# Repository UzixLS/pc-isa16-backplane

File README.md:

## ISA16-BACKPLANE
Compact ISA 16-bit backplane board

Specs:
- 171x155mm
- 7 ISA 16-bit (98 pin) slots
- ATX 20 pin power supply connector
- ATX power control circuit
- LEDs for +5V, +12V, -5V, -12V and standby power rails
- Power button
- Headers for power button and +5V power led

### Changelog
* Rev.A - first release
* Rev.A1 - ATX connector changed from 5.5mm to 4.4mm and rotated 180°

### See also
* ISA 8-bit backplane by Sergey Kiselev: [link](https://github.com/skiselev/isa8_backplane)
* ISA 16-bit backplane by Alexandru Groza: [link](https://alexandrugroza.ro/microelectronics/system-design/isa-backplane/index.html)

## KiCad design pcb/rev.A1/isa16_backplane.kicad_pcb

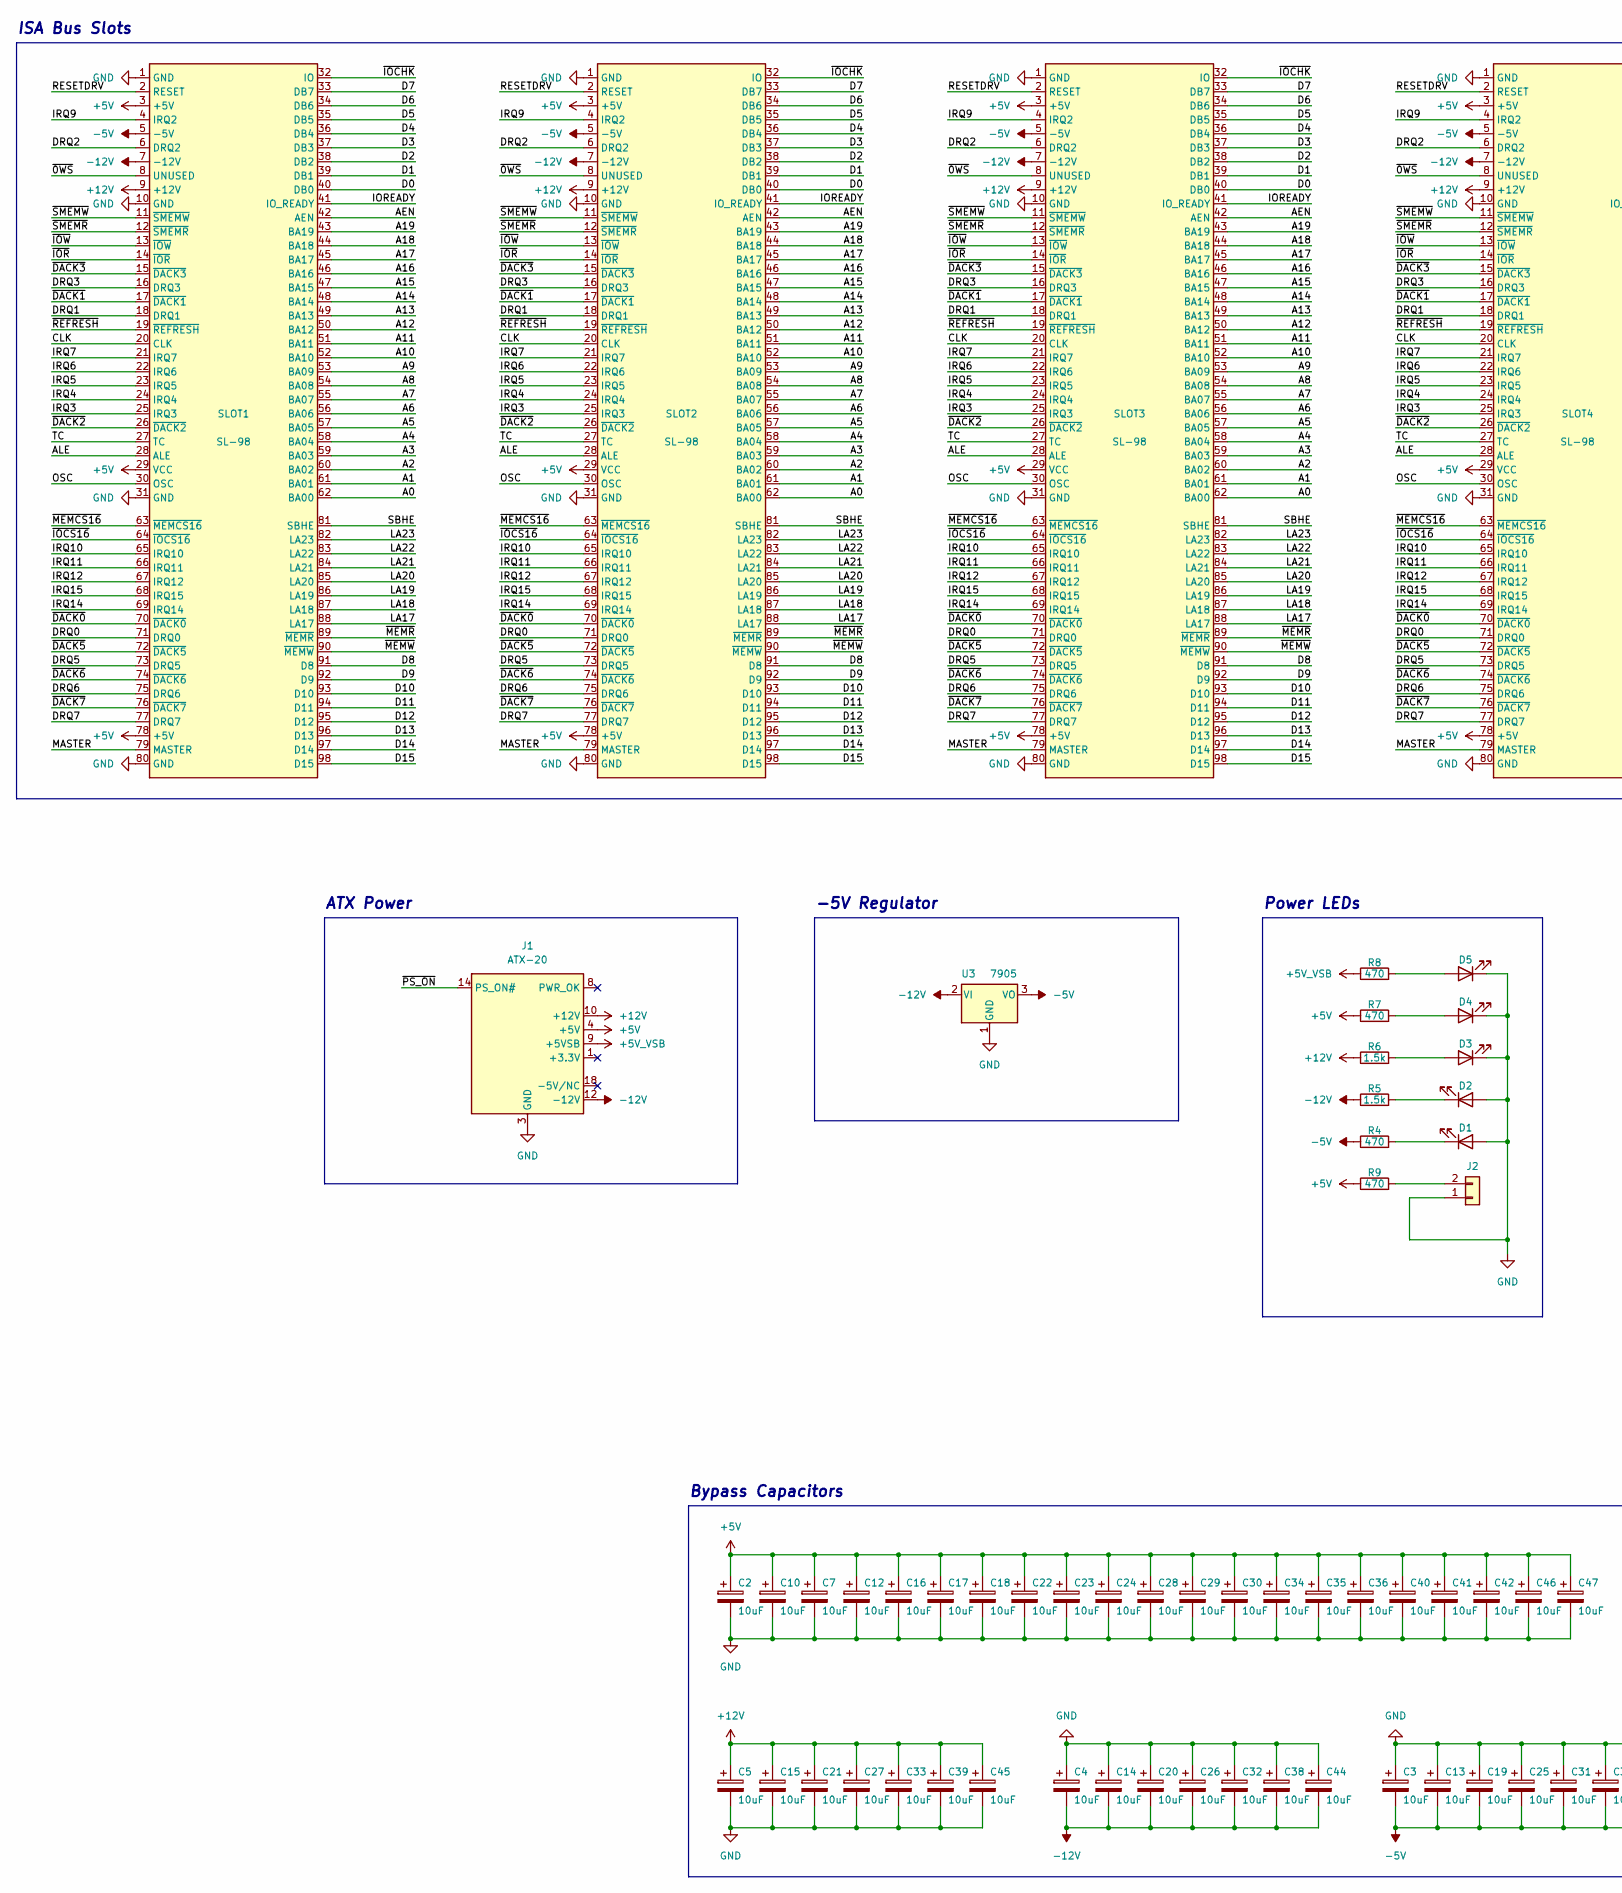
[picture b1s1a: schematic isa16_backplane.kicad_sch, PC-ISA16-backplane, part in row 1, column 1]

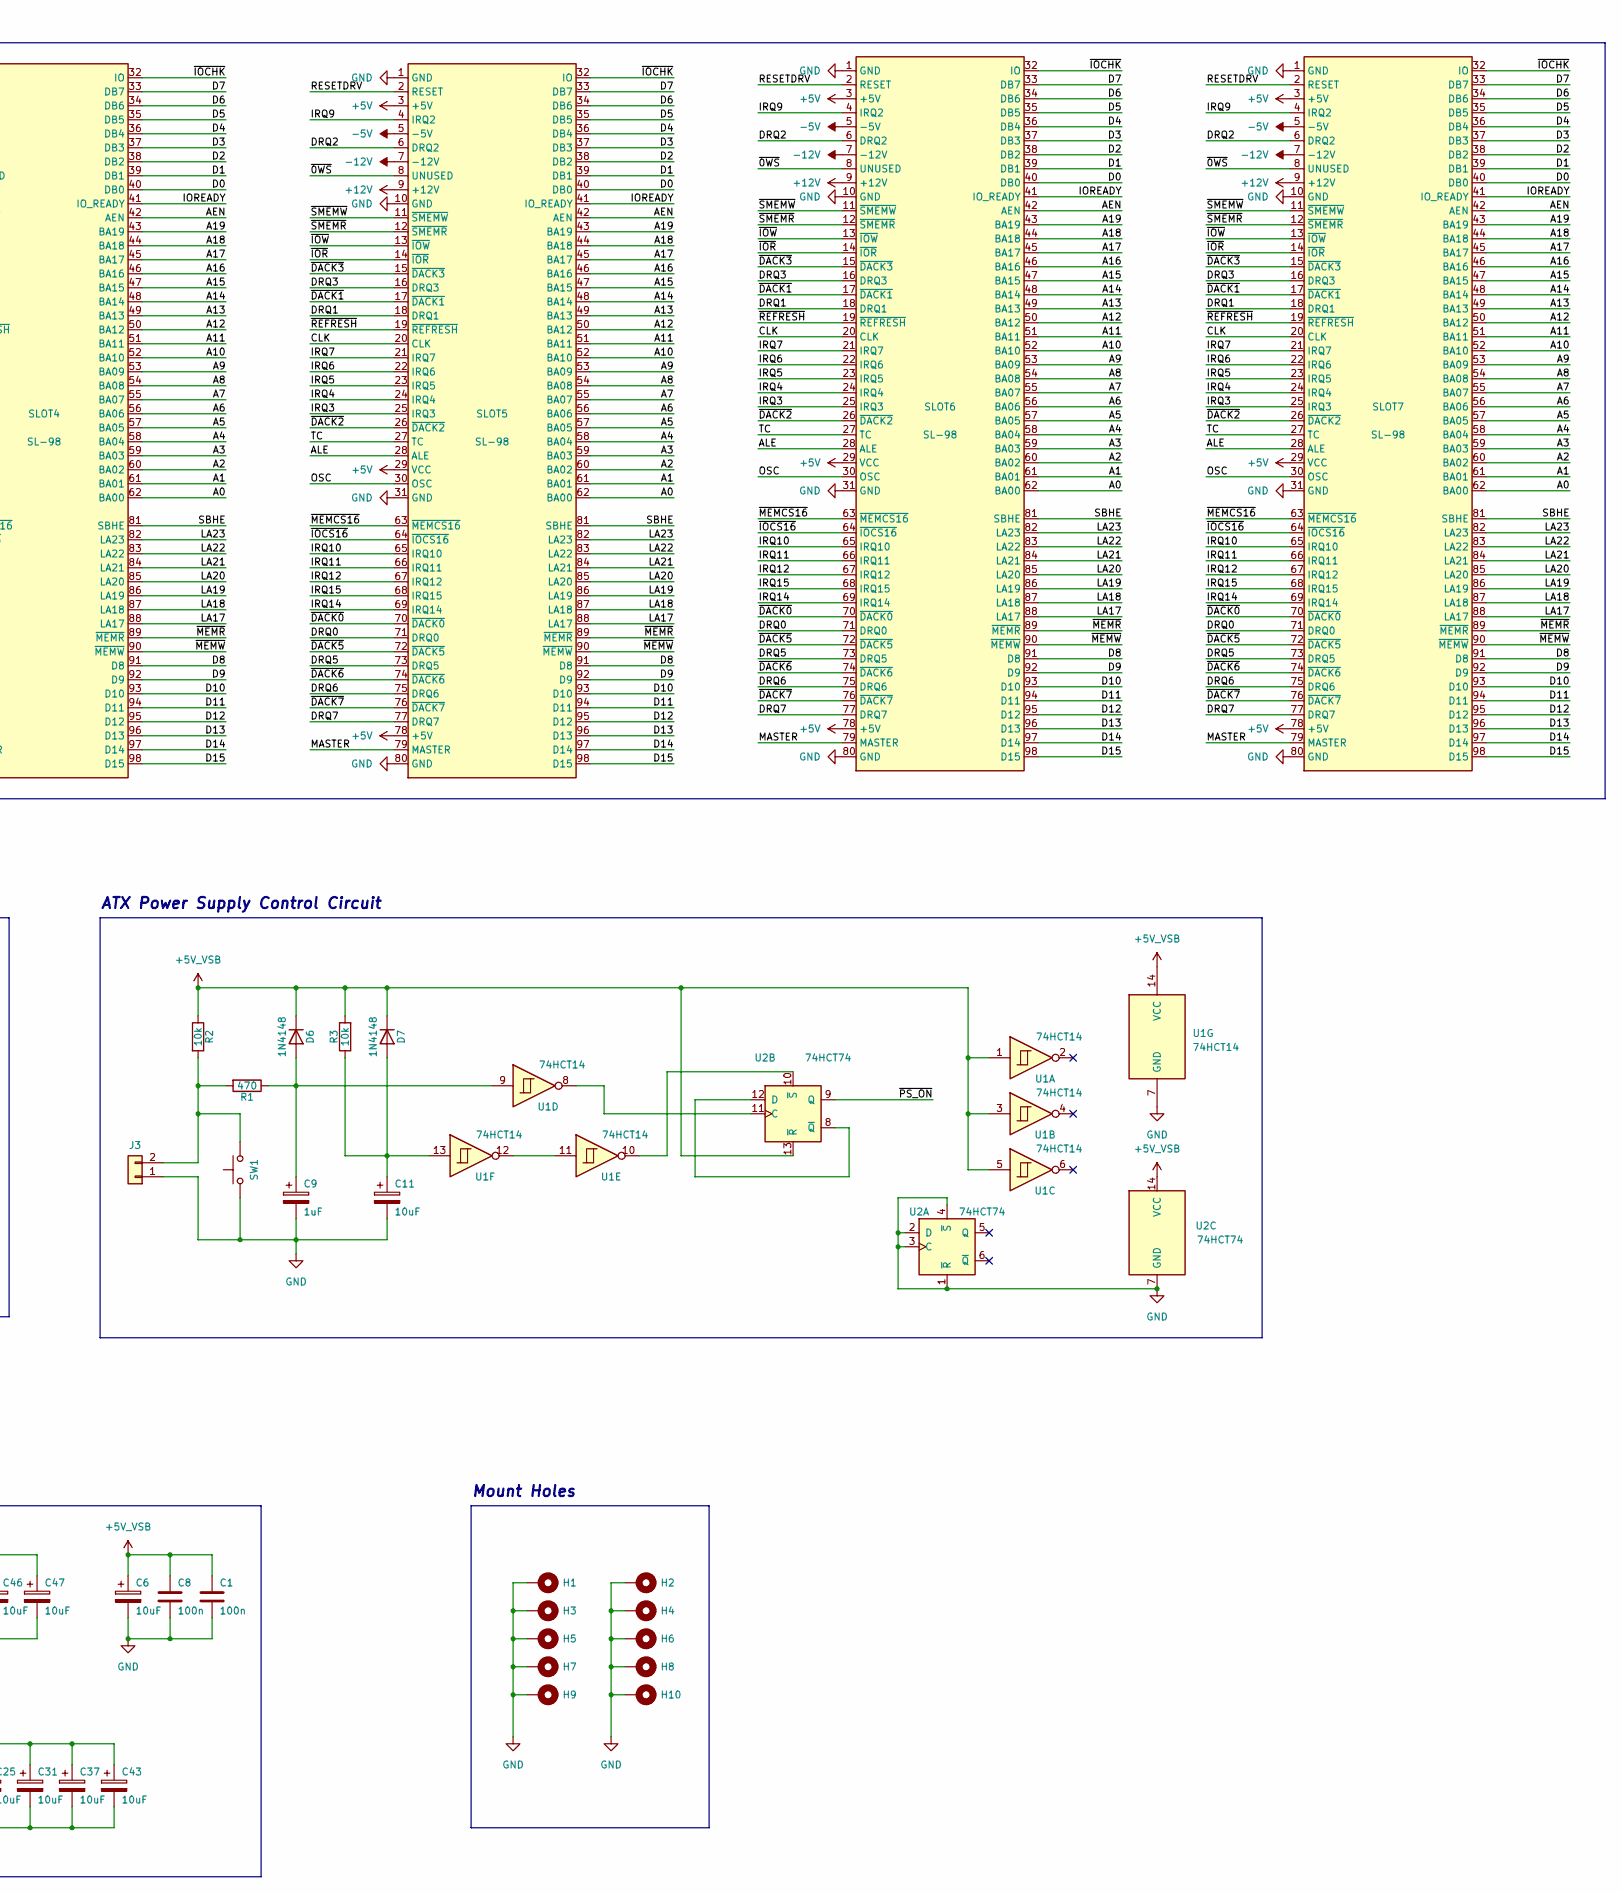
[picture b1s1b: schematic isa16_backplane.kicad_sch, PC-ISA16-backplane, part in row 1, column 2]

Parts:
C1, C8: 100n; C_Disc_D8.0mm_W2.5mm_P5.00mm
C2, C3, C4, C5, C6, C7, C10, C11, C12, C13, C14, C15, C16, C17, C18, C19, C20, C21, C22, C23, C24, C25, C26, C27, C28, C29, C30, C31, C32, C33, C34, C35, C36, C37, C38, C39, C40, C41, C42, C43, C44, C45, C46, C47: 10uF; CP_Radial_Tantal_D5.0mm_P5.00mm
C9: 1uF; CP_Radial_Tantal_D5.0mm_P5.00mm
D1, D2, D3, D4, D5: LED; LED_D5.0mm
D6, D7: 1N4148; D_DO-35_SOD27_P7.62mm_Horizontal
H1, H2, H3, H4, H5, H6, H7, H8, H9, H10: MountingHole_Pad; MountingHole_4mm_Pad_Via
J1: ATX-20; Conn_Power_ATX_20pin_4.4mm
J2, J3: Conn_01x02; PinHeader_1x02_P2.54mm_Vertical
R1, R4, R7, R8, R9: 470; R_Axial_DIN0207_L6.3mm_D2.5mm_P7.62mm_Horizontal
R2, R3: 10k; R_Axial_DIN0207_L6.3mm_D2.5mm_P7.62mm_Horizontal
R5, R6: 1.5k; R_Axial_DIN0207_L6.3mm_D2.5mm_P7.62mm_Horizontal
SLOT1, SLOT2, SLOT3, SLOT4, SLOT5, SLOT6, SLOT7: SL-98; ISA16_Slot
SW1: SW_Push; SW_PUSH_6mm
U1: 74HCT14; DIP-14_W7.62mm
U2: 74HCT74; DIP-14_W7.62mm
U3: 7905; TO-220-3_Horizontal_TabDownPin2

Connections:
+5V: C2.1, C7.1, C10.1, C12.1, C16.1, C17.1, C18.1, C22.1, C23.1, C24.1, C28.1, C29.1, C30.1, C34.1, C35.1, C36.1, C40.1, C41.1, C42.1, C46.1, C47.1, J1.4 (+5V), J1.6 (+5V), J1.19 (+5V), J1.20 (+5V), R7.1, R9.1, SLOT1.3 (+5V), SLOT1.29 (VCC), SLOT1.78 (+5V), SLOT2.3 (+5V), SLOT2.29 (VCC), SLOT2.78 (+5V), SLOT3.3 (+5V), SLOT3.29 (VCC), SLOT3.78 (+5V), SLOT4.3 (+5V), SLOT4.29 (VCC), SLOT4.78 (+5V), SLOT5.3 (+5V), SLOT5.29 (VCC), SLOT5.78 (+5V), SLOT6.3 (+5V), SLOT6.29 (VCC), SLOT6.78 (+5V), SLOT7.3 (+5V), SLOT7.29 (VCC), SLOT7.78 (+5V)
+5V_VSB: C1.1, C6.1, C8.1, D6.1 (K), D7.1 (K), J1.9 (+5VSB), R2.1, R3.2, R8.1, U1.1, U1.3, U1.5, U1.14 (VCC), U2.13 (~R), U2.14 (VCC)
+12V: C5.1, C15.1, C21.1, C27.1, C33.1, C39.1, C45.1, J1.10 (+12V), R6.1, SLOT1.9 (+12V), SLOT2.9 (+12V), SLOT3.9 (+12V), SLOT4.9 (+12V), SLOT5.9 (+12V), SLOT6.9 (+12V), SLOT7.9 (+12V)
-5V: C3.2, C13.2, C19.2, C25.2, C31.2, C37.2, C43.2, R4.1, SLOT1.5 (-5V), SLOT2.5 (-5V), SLOT3.5 (-5V), SLOT4.5 (-5V), SLOT5.5 (-5V), SLOT6.5 (-5V), SLOT7.5 (-5V), U3.3 (VO)
-12V: C4.2, C14.2, C20.2, C26.2, C32.2, C38.2, C44.2, J1.12 (-12V), R5.1, SLOT1.7 (-12V), SLOT2.7 (-12V), SLOT3.7 (-12V), SLOT4.7 (-12V), SLOT5.7 (-12V), SLOT6.7 (-12V), SLOT7.7 (-12V), U3.2 (VI)
/A0: SLOT1.62 (BA00), SLOT2.62 (BA00), SLOT3.62 (BA00), SLOT4.62 (BA00), SLOT5.62 (BA00), SLOT6.62 (BA00), SLOT7.62 (BA00)
/A1: SLOT1.61 (BA01), SLOT2.61 (BA01), SLOT3.61 (BA01), SLOT4.61 (BA01), SLOT5.61 (BA01), SLOT6.61 (BA01), SLOT7.61 (BA01)
/A2: SLOT1.60 (BA02), SLOT2.60 (BA02), SLOT3.60 (BA02), SLOT4.60 (BA02), SLOT5.60 (BA02), SLOT6.60 (BA02), SLOT7.60 (BA02)
/A3: SLOT1.59 (BA03), SLOT2.59 (BA03), SLOT3.59 (BA03), SLOT4.59 (BA03), SLOT5.59 (BA03), SLOT6.59 (BA03), SLOT7.59 (BA03)
/A4: SLOT1.58 (BA04), SLOT2.58 (BA04), SLOT3.58 (BA04), SLOT4.58 (BA04), SLOT5.58 (BA04), SLOT6.58 (BA04), SLOT7.58 (BA04)
/A5: SLOT1.57 (BA05), SLOT2.57 (BA05), SLOT3.57 (BA05), SLOT4.57 (BA05), SLOT5.57 (BA05), SLOT6.57 (BA05), SLOT7.57 (BA05)
/A6: SLOT1.56 (BA06), SLOT2.56 (BA06), SLOT3.56 (BA06), SLOT4.56 (BA06), SLOT5.56 (BA06), SLOT6.56 (BA06), SLOT7.56 (BA06)
/A7: SLOT1.55 (BA07), SLOT2.55 (BA07), SLOT3.55 (BA07), SLOT4.55 (BA07), SLOT5.55 (BA07), SLOT6.55 (BA07), SLOT7.55 (BA07)
/A8: SLOT1.54 (BA08), SLOT2.54 (BA08), SLOT3.54 (BA08), SLOT4.54 (BA08), SLOT5.54 (BA08), SLOT6.54 (BA08), SLOT7.54 (BA08)
/A9: SLOT1.53 (BA09), SLOT2.53 (BA09), SLOT3.53 (BA09), SLOT4.53 (BA09), SLOT5.53 (BA09), SLOT6.53 (BA09), SLOT7.53 (BA09)
/A10: SLOT1.52 (BA10), SLOT2.52 (BA10), SLOT3.52 (BA10), SLOT4.52 (BA10), SLOT5.52 (BA10), SLOT6.52 (BA10), SLOT7.52 (BA10)
/A11: SLOT1.51 (BA11), SLOT2.51 (BA11), SLOT3.51 (BA11), SLOT4.51 (BA11), SLOT5.51 (BA11), SLOT6.51 (BA11), SLOT7.51 (BA11)
/A12: SLOT1.50 (BA12), SLOT2.50 (BA12), SLOT3.50 (BA12), SLOT4.50 (BA12), SLOT5.50 (BA12), SLOT6.50 (BA12), SLOT7.50 (BA12)
/A13: SLOT1.49 (BA13), SLOT2.49 (BA13), SLOT3.49 (BA13), SLOT4.49 (BA13), SLOT5.49 (BA13), SLOT6.49 (BA13), SLOT7.49 (BA13)
/A14: SLOT1.48 (BA14), SLOT2.48 (BA14), SLOT3.48 (BA14), SLOT4.48 (BA14), SLOT5.48 (BA14), SLOT6.48 (BA14), SLOT7.48 (BA14)
/A15: SLOT1.47 (BA15), SLOT2.47 (BA15), SLOT3.47 (BA15), SLOT4.47 (BA15), SLOT5.47 (BA15), SLOT6.47 (BA15), SLOT7.47 (BA15)
/A16: SLOT1.46 (BA16), SLOT2.46 (BA16), SLOT3.46 (BA16), SLOT4.46 (BA16), SLOT5.46 (BA16), SLOT6.46 (BA16), SLOT7.46 (BA16)
/A17: SLOT1.45 (BA17), SLOT2.45 (BA17), SLOT3.45 (BA17), SLOT4.45 (BA17), SLOT5.45 (BA17), SLOT6.45 (BA17), SLOT7.45 (BA17)
/A18: SLOT1.44 (BA18), SLOT2.44 (BA18), SLOT3.44 (BA18), SLOT4.44 (BA18), SLOT5.44 (BA18), SLOT6.44 (BA18), SLOT7.44 (BA18)
/A19: SLOT1.43 (BA19), SLOT2.43 (BA19), SLOT3.43 (BA19), SLOT4.43 (BA19), SLOT5.43 (BA19), SLOT6.43 (BA19), SLOT7.43 (BA19)
/AEN: SLOT1.42 (AEN), SLOT2.42 (AEN), SLOT3.42 (AEN), SLOT4.42 (AEN), SLOT5.42 (AEN), SLOT6.42 (AEN), SLOT7.42 (AEN)
/ALE: SLOT1.28 (ALE), SLOT2.28 (ALE), SLOT3.28 (ALE), SLOT4.28 (ALE), SLOT5.28 (ALE), SLOT6.28 (ALE), SLOT7.28 (ALE)
/CLK: SLOT1.20 (CLK), SLOT2.20 (CLK), SLOT3.20 (CLK), SLOT4.20 (CLK), SLOT5.20 (CLK), SLOT6.20 (CLK), SLOT7.20 (CLK)
/D0: SLOT1.40 (DB0), SLOT2.40 (DB0), SLOT3.40 (DB0), SLOT4.40 (DB0), SLOT5.40 (DB0), SLOT6.40 (DB0), SLOT7.40 (DB0)
/D1: SLOT1.39 (DB1), SLOT2.39 (DB1), SLOT3.39 (DB1), SLOT4.39 (DB1), SLOT5.39 (DB1), SLOT6.39 (DB1), SLOT7.39 (DB1)
/D2: SLOT1.38 (DB2), SLOT2.38 (DB2), SLOT3.38 (DB2), SLOT4.38 (DB2), SLOT5.38 (DB2), SLOT6.38 (DB2), SLOT7.38 (DB2)
/D3: SLOT1.37 (DB3), SLOT2.37 (DB3), SLOT3.37 (DB3), SLOT4.37 (DB3), SLOT5.37 (DB3), SLOT6.37 (DB3), SLOT7.37 (DB3)
/D4: SLOT1.36 (DB4), SLOT2.36 (DB4), SLOT3.36 (DB4), SLOT4.36 (DB4), SLOT5.36 (DB4), SLOT6.36 (DB4), SLOT7.36 (DB4)
/D5: SLOT1.35 (DB5), SLOT2.35 (DB5), SLOT3.35 (DB5), SLOT4.35 (DB5), SLOT5.35 (DB5), SLOT6.35 (DB5), SLOT7.35 (DB5)
/D6: SLOT1.34 (DB6), SLOT2.34 (DB6), SLOT3.34 (DB6), SLOT4.34 (DB6), SLOT5.34 (DB6), SLOT6.34 (DB6), SLOT7.34 (DB6)
/D7: SLOT1.33 (DB7), SLOT2.33 (DB7), SLOT3.33 (DB7), SLOT4.33 (DB7), SLOT5.33 (DB7), SLOT6.33 (DB7), SLOT7.33 (DB7)
/D8: SLOT1.91 (D8), SLOT2.91 (D8), SLOT3.91 (D8), SLOT4.91 (D8), SLOT5.91 (D8), SLOT6.91 (D8), SLOT7.91 (D8)
/D9: SLOT1.92 (D9), SLOT2.92 (D9), SLOT3.92 (D9), SLOT4.92 (D9), SLOT5.92 (D9), SLOT6.92 (D9), SLOT7.92 (D9)
/D10: SLOT1.93 (D10), SLOT2.93 (D10), SLOT3.93 (D10), SLOT4.93 (D10), SLOT5.93 (D10), SLOT6.93 (D10), SLOT7.93 (D10)
/D11: SLOT1.94 (D11), SLOT2.94 (D11), SLOT3.94 (D11), SLOT4.94 (D11), SLOT5.94 (D11), SLOT6.94 (D11), SLOT7.94 (D11)
/D12: SLOT1.95 (D12), SLOT2.95 (D12), SLOT3.95 (D12), SLOT4.95 (D12), SLOT5.95 (D12), SLOT6.95 (D12), SLOT7.95 (D12)
/D13: SLOT1.96 (D13), SLOT2.96 (D13), SLOT3.96 (D13), SLOT4.96 (D13), SLOT5.96 (D13), SLOT6.96 (D13), SLOT7.96 (D13)
/D14: SLOT1.97 (D14), SLOT2.97 (D14), SLOT3.97 (D14), SLOT4.97 (D14), SLOT5.97 (D14), SLOT6.97 (D14), SLOT7.97 (D14)
/D15: SLOT1.98 (D15), SLOT2.98 (D15), SLOT3.98 (D15), SLOT4.98 (D15), SLOT5.98 (D15), SLOT6.98 (D15), SLOT7.98 (D15)
/DRQ0: SLOT1.71 (DRQ0), SLOT2.71 (DRQ0), SLOT3.71 (DRQ0), SLOT4.71 (DRQ0), SLOT5.71 (DRQ0), SLOT6.71 (DRQ0), SLOT7.71 (DRQ0)
/DRQ1: SLOT1.18 (DRQ1), SLOT2.18 (DRQ1), SLOT3.18 (DRQ1), SLOT4.18 (DRQ1), SLOT5.18 (DRQ1), SLOT6.18 (DRQ1), SLOT7.18 (DRQ1)
/DRQ2: SLOT1.6 (DRQ2), SLOT2.6 (DRQ2), SLOT3.6 (DRQ2), SLOT4.6 (DRQ2), SLOT5.6 (DRQ2), SLOT6.6 (DRQ2), SLOT7.6 (DRQ2)
/DRQ3: SLOT1.16 (DRQ3), SLOT2.16 (DRQ3), SLOT3.16 (DRQ3), SLOT4.16 (DRQ3), SLOT5.16 (DRQ3), SLOT6.16 (DRQ3), SLOT7.16 (DRQ3)
/DRQ5: SLOT1.73 (DRQ5), SLOT2.73 (DRQ5), SLOT3.73 (DRQ5), SLOT4.73 (DRQ5), SLOT5.73 (DRQ5), SLOT6.73 (DRQ5), SLOT7.73 (DRQ5)
/DRQ6: SLOT1.75 (DRQ6), SLOT2.75 (DRQ6), SLOT3.75 (DRQ6), SLOT4.75 (DRQ6), SLOT5.75 (DRQ6), SLOT6.75 (DRQ6), SLOT7.75 (DRQ6)
/DRQ7: SLOT1.77 (DRQ7), SLOT2.77 (DRQ7), SLOT3.77 (DRQ7), SLOT4.77 (DRQ7), SLOT5.77 (DRQ7), SLOT6.77 (DRQ7), SLOT7.77 (DRQ7)
/IOREADY: SLOT1.41 (IO_READY), SLOT2.41 (IO_READY), SLOT3.41 (IO_READY), SLOT4.41 (IO_READY), SLOT5.41 (IO_READY), SLOT6.41 (IO_READY), SLOT7.41 (IO_READY)
/IRQ3: SLOT1.25 (IRQ3), SLOT2.25 (IRQ3), SLOT3.25 (IRQ3), SLOT4.25 (IRQ3), SLOT5.25 (IRQ3), SLOT6.25 (IRQ3), SLOT7.25 (IRQ3)
/IRQ4: SLOT1.24 (IRQ4), SLOT2.24 (IRQ4), SLOT3.24 (IRQ4), SLOT4.24 (IRQ4), SLOT5.24 (IRQ4), SLOT6.24 (IRQ4), SLOT7.24 (IRQ4)
/IRQ5: SLOT1.23 (IRQ5), SLOT2.23 (IRQ5), SLOT3.23 (IRQ5), SLOT4.23 (IRQ5), SLOT5.23 (IRQ5), SLOT6.23 (IRQ5), SLOT7.23 (IRQ5)
/IRQ6: SLOT1.22 (IRQ6), SLOT2.22 (IRQ6), SLOT3.22 (IRQ6), SLOT4.22 (IRQ6), SLOT5.22 (IRQ6), SLOT6.22 (IRQ6), SLOT7.22 (IRQ6)
/IRQ7: SLOT1.21 (IRQ7), SLOT2.21 (IRQ7), SLOT3.21 (IRQ7), SLOT4.21 (IRQ7), SLOT5.21 (IRQ7), SLOT6.21 (IRQ7), SLOT7.21 (IRQ7)
/IRQ9: SLOT1.4 (IRQ2), SLOT2.4 (IRQ2), SLOT3.4 (IRQ2), SLOT4.4 (IRQ2), SLOT5.4 (IRQ2), SLOT6.4 (IRQ2), SLOT7.4 (IRQ2)
/IRQ10: SLOT1.65 (IRQ10), SLOT2.65 (IRQ10), SLOT3.65 (IRQ10), SLOT4.65 (IRQ10), SLOT5.65 (IRQ10), SLOT6.65 (IRQ10), SLOT7.65 (IRQ10)
/IRQ11: SLOT1.66 (IRQ11), SLOT2.66 (IRQ11), SLOT3.66 (IRQ11), SLOT4.66 (IRQ11), SLOT5.66 (IRQ11), SLOT6.66 (IRQ11), SLOT7.66 (IRQ11)
/IRQ12: SLOT1.67 (IRQ12), SLOT2.67 (IRQ12), SLOT3.67 (IRQ12), SLOT4.67 (IRQ12), SLOT5.67 (IRQ12), SLOT6.67 (IRQ12), SLOT7.67 (IRQ12)
/IRQ14: SLOT1.69 (IRQ14), SLOT2.69 (IRQ14), SLOT3.69 (IRQ14), SLOT4.69 (IRQ14), SLOT5.69 (IRQ14), SLOT6.69 (IRQ14), SLOT7.69 (IRQ14)
/IRQ15: SLOT1.68 (IRQ15), SLOT2.68 (IRQ15), SLOT3.68 (IRQ15), SLOT4.68 (IRQ15), SLOT5.68 (IRQ15), SLOT6.68 (IRQ15), SLOT7.68 (IRQ15)
/LA17: SLOT1.88 (LA17), SLOT2.88 (LA17), SLOT3.88 (LA17), SLOT4.88 (LA17), SLOT5.88 (LA17), SLOT6.88 (LA17), SLOT7.88 (LA17)
/LA18: SLOT1.87 (LA18), SLOT2.87 (LA18), SLOT3.87 (LA18), SLOT4.87 (LA18), SLOT5.87 (LA18), SLOT6.87 (LA18), SLOT7.87 (LA18)
/LA19: SLOT1.86 (LA19), SLOT2.86 (LA19), SLOT3.86 (LA19), SLOT4.86 (LA19), SLOT5.86 (LA19), SLOT6.86 (LA19), SLOT7.86 (LA19)
/LA20: SLOT1.85 (LA20), SLOT2.85 (LA20), SLOT3.85 (LA20), SLOT4.85 (LA20), SLOT5.85 (LA20), SLOT6.85 (LA20), SLOT7.85 (LA20)
/LA21: SLOT1.84 (LA21), SLOT2.84 (LA21), SLOT3.84 (LA21), SLOT4.84 (LA21), SLOT5.84 (LA21), SLOT6.84 (LA21), SLOT7.84 (LA21)
/LA22: SLOT1.83 (LA22), SLOT2.83 (LA22), SLOT3.83 (LA22), SLOT4.83 (LA22), SLOT5.83 (LA22), SLOT6.83 (LA22), SLOT7.83 (LA22)
/LA23: SLOT1.82 (LA23), SLOT2.82 (LA23), SLOT3.82 (LA23), SLOT4.82 (LA23), SLOT5.82 (LA23), SLOT6.82 (LA23), SLOT7.82 (LA23)
/MASTER: SLOT1.79 (MASTER), SLOT2.79 (MASTER), SLOT3.79 (MASTER), SLOT4.79 (MASTER), SLOT5.79 (MASTER), SLOT6.79 (MASTER), SLOT7.79 (MASTER)
/OSC: SLOT1.30 (OSC), SLOT2.30 (OSC), SLOT3.30 (OSC), SLOT4.30 (OSC), SLOT5.30 (OSC), SLOT6.30 (OSC), SLOT7.30 (OSC)
/RESETDRV: SLOT1.2 (RESET), SLOT2.2 (RESET), SLOT3.2 (RESET), SLOT4.2 (RESET), SLOT5.2 (RESET), SLOT6.2 (RESET), SLOT7.2 (RESET)
/SBHE: SLOT1.81 (SBHE), SLOT2.81 (SBHE), SLOT3.81 (SBHE), SLOT4.81 (SBHE), SLOT5.81 (SBHE), SLOT6.81 (SBHE), SLOT7.81 (SBHE)
/TC: SLOT1.27 (TC), SLOT2.27 (TC), SLOT3.27 (TC), SLOT4.27 (TC), SLOT5.27 (TC), SLOT6.27 (TC), SLOT7.27 (TC)
/~0WS: SLOT1.8 (UNUSED), SLOT2.8 (UNUSED), SLOT3.8 (UNUSED), SLOT4.8 (UNUSED), SLOT5.8 (UNUSED), SLOT6.8 (UNUSED), SLOT7.8 (UNUSED)
/~DACK0: SLOT1.70 (~DACK0), SLOT2.70 (~DACK0), SLOT3.70 (~DACK0), SLOT4.70 (~DACK0), SLOT5.70 (~DACK0), SLOT6.70 (~DACK0), SLOT7.70 (~DACK0)
/~DACK1: SLOT1.17 (~DACK1), SLOT2.17 (~DACK1), SLOT3.17 (~DACK1), SLOT4.17 (~DACK1), SLOT5.17 (~DACK1), SLOT6.17 (~DACK1), SLOT7.17 (~DACK1)
/~DACK2: SLOT1.26 (~DACK2), SLOT2.26 (~DACK2), SLOT3.26 (~DACK2), SLOT4.26 (~DACK2), SLOT5.26 (~DACK2), SLOT6.26 (~DACK2), SLOT7.26 (~DACK2)
/~DACK3: SLOT1.15 (~DACK3), SLOT2.15 (~DACK3), SLOT3.15 (~DACK3), SLOT4.15 (~DACK3), SLOT5.15 (~DACK3), SLOT6.15 (~DACK3), SLOT7.15 (~DACK3)
/~DACK5: SLOT1.72 (~DACK5), SLOT2.72 (~DACK5), SLOT3.72 (~DACK5), SLOT4.72 (~DACK5), SLOT5.72 (~DACK5), SLOT6.72 (~DACK5), SLOT7.72 (~DACK5)
/~DACK6: SLOT1.74 (~DACK6), SLOT2.74 (~DACK6), SLOT3.74 (~DACK6), SLOT4.74 (~DACK6), SLOT5.74 (~DACK6), SLOT6.74 (~DACK6), SLOT7.74 (~DACK6)
/~DACK7: SLOT1.76 (~DACK7), SLOT2.76 (~DACK7), SLOT3.76 (~DACK7), SLOT4.76 (~DACK7), SLOT5.76 (~DACK7), SLOT6.76 (~DACK7), SLOT7.76 (~DACK7)
/~IOCHK: SLOT1.32 (IO), SLOT2.32 (IO), SLOT3.32 (IO), SLOT4.32 (IO), SLOT5.32 (IO), SLOT6.32 (IO), SLOT7.32 (IO)
/~IOCS16: SLOT1.64 (~IOCS16), SLOT2.64 (~IOCS16), SLOT3.64 (~IOCS16), SLOT4.64 (~IOCS16), SLOT5.64 (~IOCS16), SLOT6.64 (~IOCS16), SLOT7.64 (~IOCS16)
/~IOR: SLOT1.14 (~IOR), SLOT2.14 (~IOR), SLOT3.14 (~IOR), SLOT4.14 (~IOR), SLOT5.14 (~IOR), SLOT6.14 (~IOR), SLOT7.14 (~IOR)
/~IOW: SLOT1.13 (~IOW), SLOT2.13 (~IOW), SLOT3.13 (~IOW), SLOT4.13 (~IOW), SLOT5.13 (~IOW), SLOT6.13 (~IOW), SLOT7.13 (~IOW)
/~MEMCS16: SLOT1.63 (~MEMCS16), SLOT2.63 (~MEMCS16), SLOT3.63 (~MEMCS16), SLOT4.63 (~MEMCS16), SLOT5.63 (~MEMCS16), SLOT6.63 (~MEMCS16), SLOT7.63 (~MEMCS16)
/~MEMR: SLOT1.89 (~MEMR), SLOT2.89 (~MEMR), SLOT3.89 (~MEMR), SLOT4.89 (~MEMR), SLOT5.89 (~MEMR), SLOT6.89 (~MEMR), SLOT7.89 (~MEMR)
/~MEMW: SLOT1.90 (~MEMW), SLOT2.90 (~MEMW), SLOT3.90 (~MEMW), SLOT4.90 (~MEMW), SLOT5.90 (~MEMW), SLOT6.90 (~MEMW), SLOT7.90 (~MEMW)
/~PS_ON: J1.14 (PS_ON#), U2.9 (Q)
/~REFRESH: SLOT1.19 (~REFRESH), SLOT2.19 (~REFRESH), SLOT3.19 (~REFRESH), SLOT4.19 (~REFRESH), SLOT5.19 (~REFRESH), SLOT6.19 (~REFRESH), SLOT7.19 (~REFRESH)
/~SMEMR: SLOT1.12 (~SMEMR), SLOT2.12 (~SMEMR), SLOT3.12 (~SMEMR), SLOT4.12 (~SMEMR), SLOT5.12 (~SMEMR), SLOT6.12 (~SMEMR), SLOT7.12 (~SMEMR)
/~SMEMW: SLOT1.11 (~SMEMW), SLOT2.11 (~SMEMW), SLOT3.11 (~SMEMW), SLOT4.11 (~SMEMW), SLOT5.11 (~SMEMW), SLOT6.11 (~SMEMW), SLOT7.11 (~SMEMW)
GND: C1.2, C2.2, C3.1, C4.1, C5.2, C6.2, C7.2, C8.2, C9.2, C10.2, C11.2, C12.2, C13.1, C14.1, C15.2, C16.2, C17.2, C18.2, C19.1, C20.1, C21.2, C22.2, C23.2, C24.2, C25.1, C26.1, C27.2, C28.2, C29.2, C30.2, C31.1, C32.1, C33.2, C34.2, C35.2, C36.2, C37.1, C38.1, C39.2, C40.2, C41.2, C42.2, C43.1, C44.1, C45.2, C46.2, C47.2, D1.2 (A), D2.2 (A), D3.1 (K), D4.1 (K), D5.1 (K), H1.1, H2.1, H3.1, H4.1, H5.1, H6.1, H7.1, H8.1, H9.1, H10.1, J1.3 (GND), J1.5 (GND), J1.7 (GND), J1.13 (GND), J1.15 (GND), J1.16 (GND), J1.17 (GND), J2.1, J3.1, SLOT1.1 (GND), SLOT1.10 (GND), SLOT1.31 (GND), SLOT1.80 (GND), SLOT2.1 (GND), SLOT2.10 (GND), SLOT2.31 (GND), SLOT2.80 (GND), SLOT3.1 (GND), SLOT3.10 (GND), SLOT3.31 (GND), SLOT3.80 (GND), SLOT4.1 (GND), SLOT4.10 (GND), SLOT4.31 (GND), SLOT4.80 (GND), SLOT5.1 (GND), SLOT5.10 (GND), SLOT5.31 (GND), SLOT5.80 (GND), SLOT6.1 (GND), SLOT6.10 (GND), SLOT6.31 (GND), SLOT6.80 (GND), SLOT7.1 (GND), SLOT7.10 (GND), SLOT7.31 (GND), SLOT7.80 (GND), SW1.2, U1.7 (GND), U2.1 (~R), U2.2 (D), U2.3 (C), U2.4 (~S), U2.7 (GND), U3.1 (GND)
unnamed: D1.1 (K), R4.2
unnamed: D2.1 (K), R5.2
unnamed: D3.2 (A), R6.2
unnamed: D4.2 (A), R7.2
unnamed: D5.2 (A), R8.2
unnamed: C9.1, D6.2 (A), R1.1, U1.9
unnamed: C11.1, D7.2 (A), R3.1, U1.13
unnamed: J2.2, R9.2
unnamed: J3.2, R1.2, R2.2, SW1.1
unnamed: U1.11, U1.12
unnamed: U1.8, U2.11 (C)
unnamed: U2.8 (~Q), U2.12 (D)
unnamed: U1.10, U2.10 (~S)

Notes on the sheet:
ATX Power Supply Control Circuit
Bypass Capacitors
Power LEDs
-5V Regulator
Mount Holes
ATX Power
ISA Bus Slots

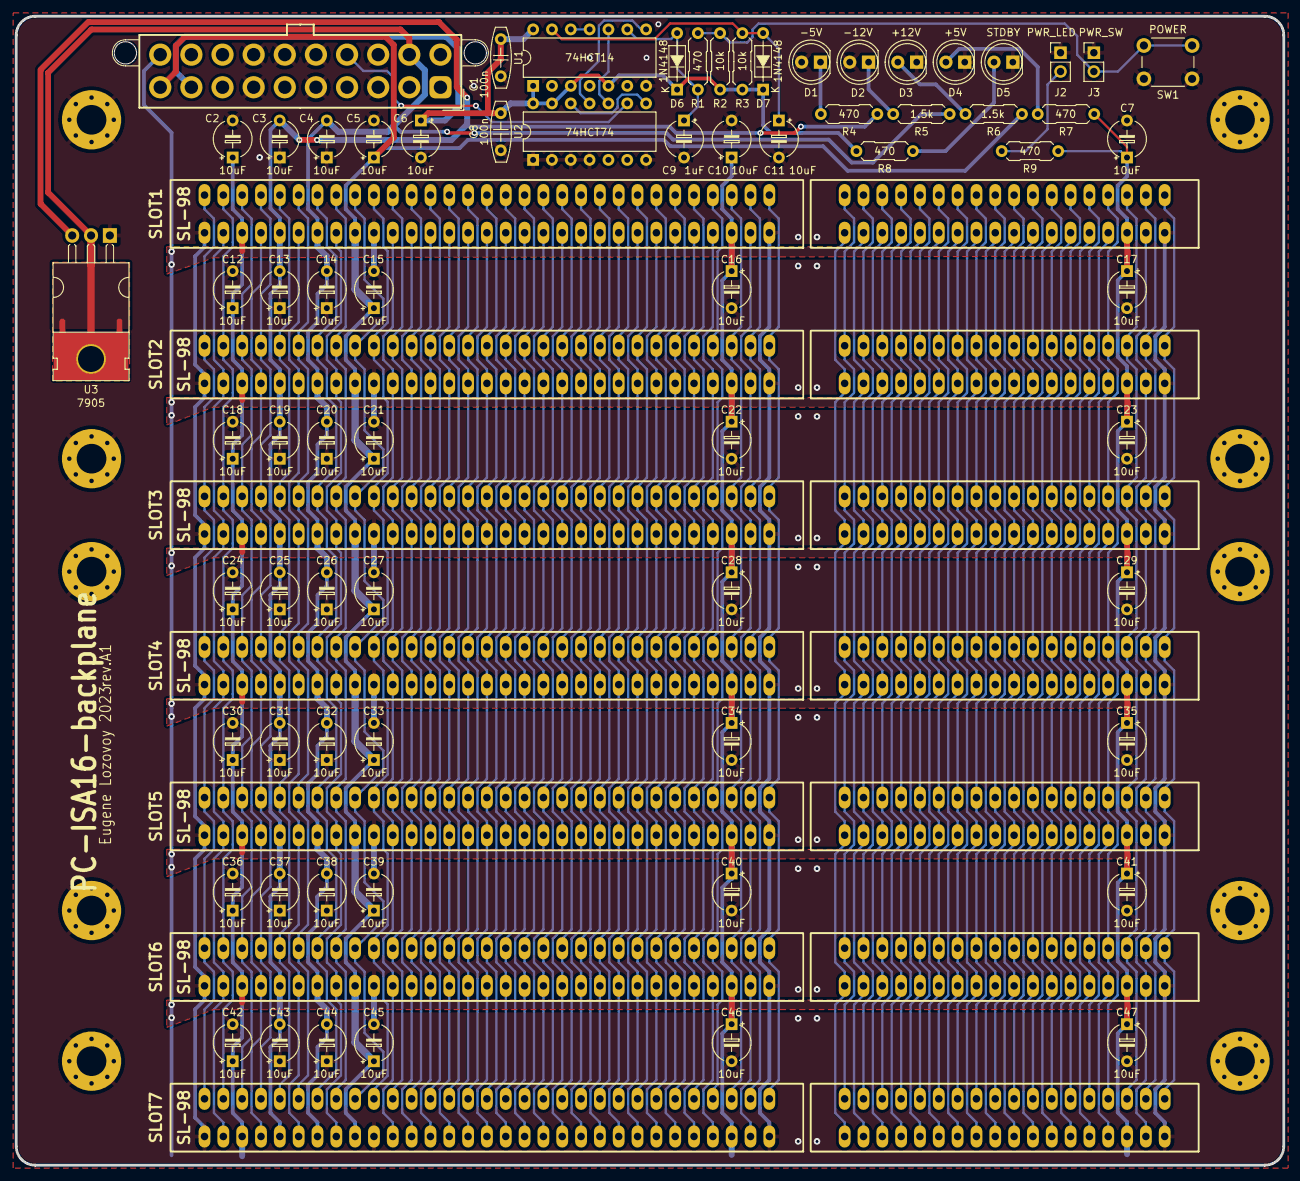
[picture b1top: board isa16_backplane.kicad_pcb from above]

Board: 2 copper layers, 171.0 x 155.0 mm, 87 parts (0 on the bottom side), 108 nets.

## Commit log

2023-05-29 init
2023-05-29 add pcb rev.A files (wip)
2023-11-17 update pcb rev.A files (final)
2023-11-17 add pcb rev.A1 files
2023-11-25 update pcb rev.A1 files (final)
2023-11-25 release pcb rev.A1
2023-11-25 add readme
2026-06-17 remove raw=true from README links
